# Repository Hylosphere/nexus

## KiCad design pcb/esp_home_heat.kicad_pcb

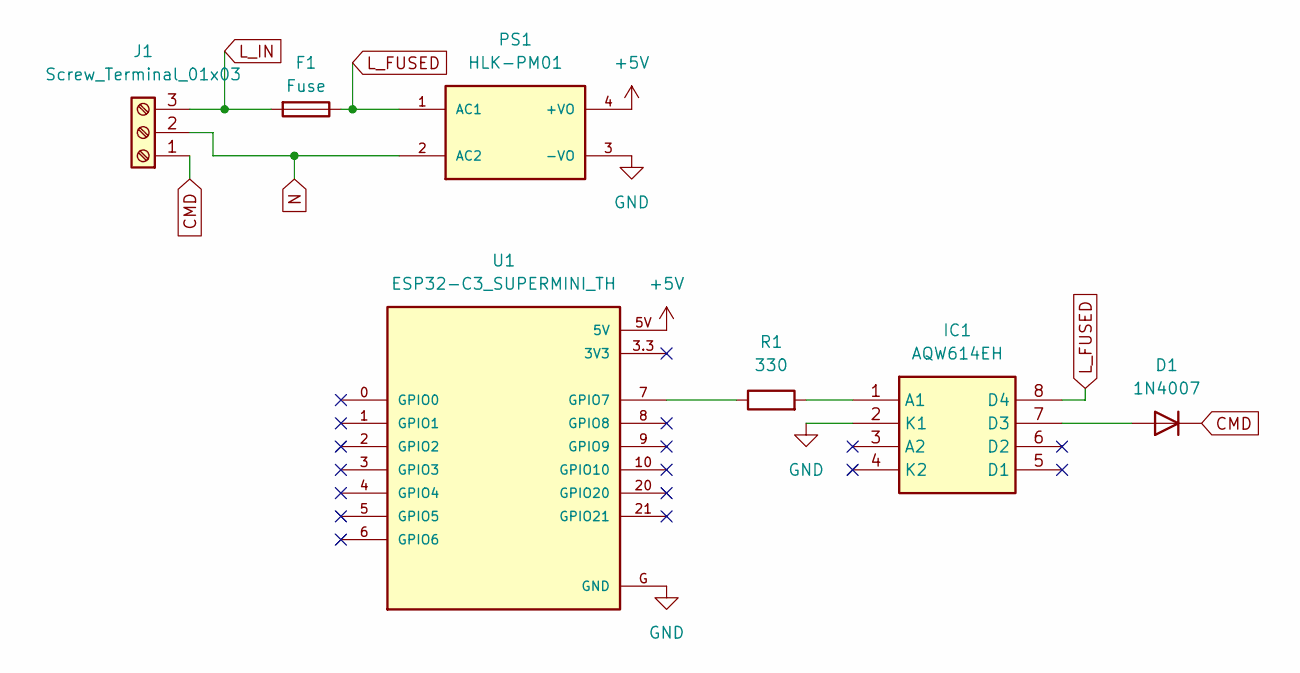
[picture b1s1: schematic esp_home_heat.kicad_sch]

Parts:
D1: 1N4007; D_DO-41_SOD81_P10.16mm_Horizontal
F1: Fuse; Fuseholder_Cylinder-5x20mm_Schurter_0031_8201_Horizontal_Op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
IC1: AQW614EH; PowerIntegrations_SMD-8; Manufacturer_Part_Number AQW614EH; Mouser Part Number 769-AQW614EH
J1: Screw_Terminal_01x03; TerminalBlock_bornier-3_P5.08mm
PS1: HLK-PM01; CONV_HLK-PM01
R1: 330; R_1812_4532Metric
U1: ESP32-C3_SUPERMINI_TH; MODULE_ESP32-C3_SUPERMINI_TH

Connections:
+5V: PS1.4 (+VO), U1.5V
CMD: D1.1 (K), J1.1
GND: IC1.2 (K1), PS1.3 (-VO), U1.G (GND)
L_FUSED: F1.1, IC1.8 (D4), PS1.1 (AC1)
L_IN: F1.2, J1.3
N: J1.2, PS1.2 (AC2)
unnamed: D1.2 (A), IC1.7 (D3)
unnamed: IC1.1 (A1), R1.2
unnamed: R1.1, U1.7 (GPIO7)

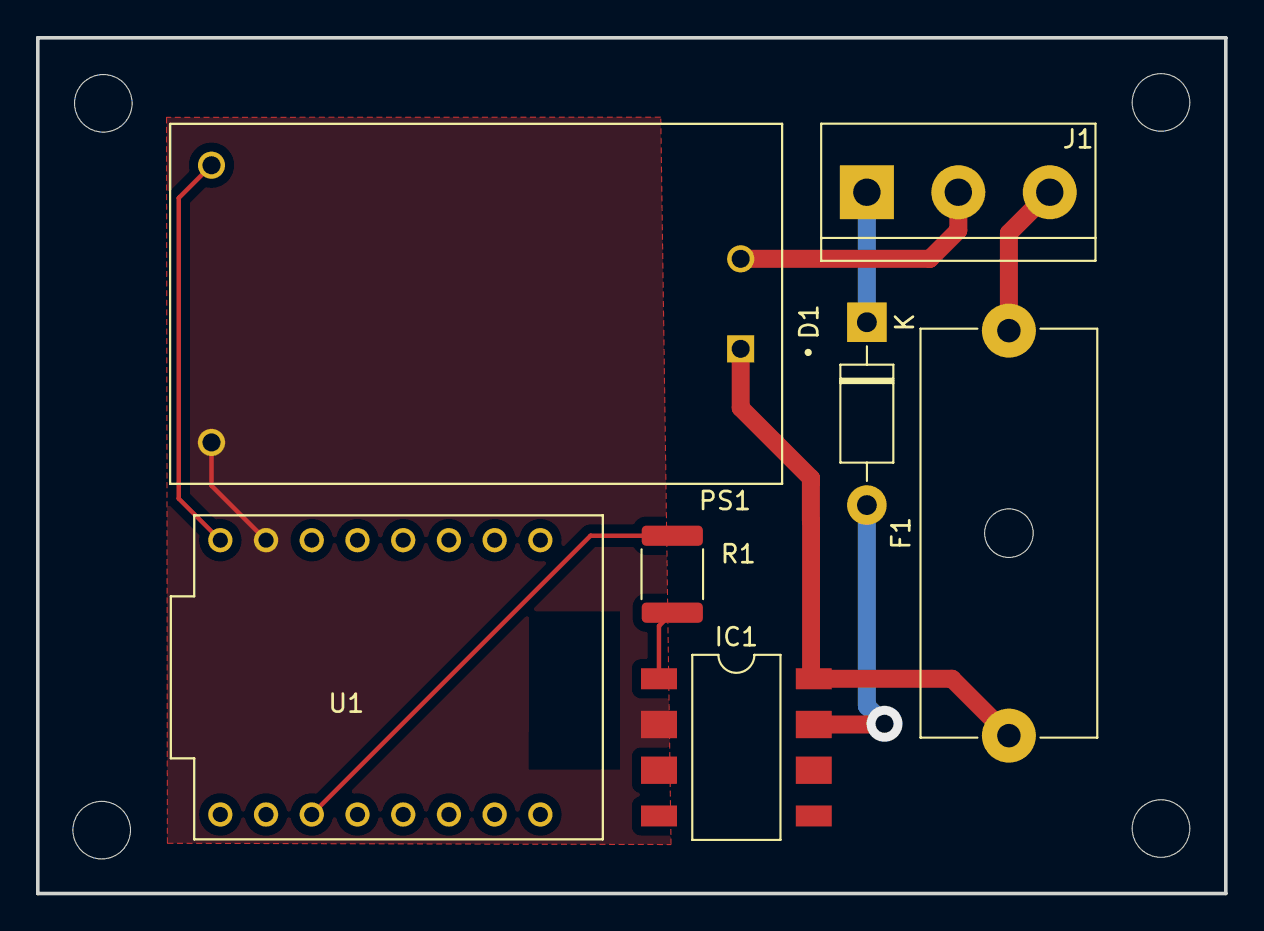
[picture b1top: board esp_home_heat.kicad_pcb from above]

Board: 2 copper layers, 66.0 x 47.5 mm, 7 parts (0 on the bottom side), 9 nets.

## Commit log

2026-02-19 Initialisation propre avec gestion des secrets
2026-03-12 toto
2026-04-03 Mise à jour du script de déploiement, ajout docker-compose et nettoyage des backups
2026-04-03 chore: remove KiCad backups folder from git tracking
2026-04-03 feat: add deployment and diff scripts to repository
